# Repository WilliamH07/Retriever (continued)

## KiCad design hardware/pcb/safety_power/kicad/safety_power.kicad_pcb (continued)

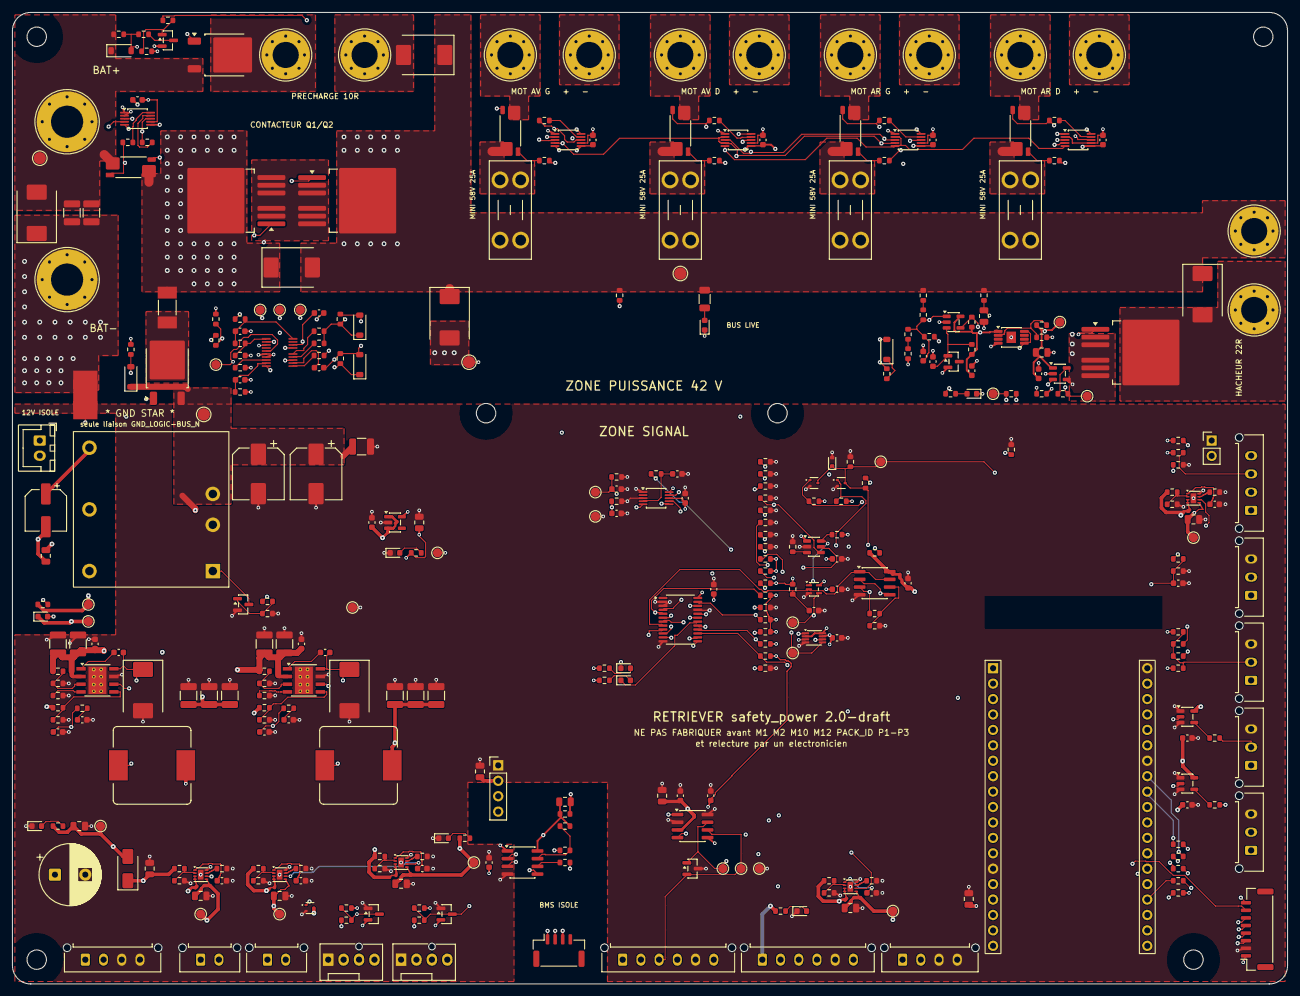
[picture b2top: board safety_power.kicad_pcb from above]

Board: 4 copper layers, 210.0 x 160.0 mm, 350 parts (0 on the bottom side), 190 nets.

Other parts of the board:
H1, H2, H3, H4, H5, H6: M3; MountingHole_3.2mm_M3

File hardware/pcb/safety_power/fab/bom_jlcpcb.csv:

Comment,Designator,Footprint,LCSC Part #
2.2µF 100V,"C1,C2,C51,CB121,CB122,CB51,CB52",C_1210_3225Metric,C153036
10µF 25V,"C10,C171,C181,C191,C201,C211,C52,C54,C57,C60,C78,C98",C_0805_2012Metric,C15850
100nF,"C11,C13,C40,C41,C42,C43,C62,C63,C64,C65,C67,C69,C71,C72,C73,C74,C75,C76,C79,C8,CB124,CB54",C_0603_1608Metric,C14663
1nF,"C12,C68",C_0603_1608Metric,C1588
1µF 25V,"C14,C53,C66,C7",C_0603_1608Metric,C5673
10nF,"C170,C180,C190,C200,C210,C70",C_0603_1608Metric,C57112
100nF 100V,"C4,CB123,CB53",C_0603_1608Metric,C88219
6.8nF,C5,C_0603_1608Metric,C1631
47µF 100V,"C50,C55",CP_Elec_8x10,C48935391
100µF 25V,C56,CP_Elec_6.3x7.7,C2836443
4.7µF 25V,"C61,C77",C_0805_2012Metric,C1779
1µF 100V,C9,C_0805_2012Metric,C385977
2200µF 10V,C99,CP_Radial_D10.0mm_P5.00mm,C49256788
15nF,CB125,C_0603_1608Metric,C107076
82pF C0G,"CB126,CB56",C_0603_1608Metric,C107056
22µF 25V,"CB127,CB128,CB129",C_1210_3225Metric,C52306
8.2nF,CB55,C_0603_1608Metric,C1322360
47µF 10V,"CB57,CB58,CB59",C_1210_3225Metric,C84494
SMCJ48CA,"D1,D2",D_SMC,C151287
KT-0603R,"D10,D11,D22",LED_0603_1608Metric,C2286
BZT52C12,"D12,D6",D_SOD-123,C43491
Everlight 19-217/GHC,"D13,D14,D15,D16,D17,D21",LED_0603_1608Metric,C72043
SS34,D18,D_SMA,C8678
NUP2105L,D19,SOT-23,C14486
ESD5Z3.3,D20,D_SOD-523,C397781
BAT54S,"D23,D24",SOT-23,C19726
B5819W,D26,D_SOD-123,C8598
SS510C,"D3,D7,D8",D_SMC,C19229
BZT52C15,"D4,D5",D_SOD-123,C173427
LM4040A25,D9,SOT-23,C9421
B560C,"DB12,DB5",D_SMC,C85100
5A 125V slo,F5,Fuse_Littelfuse-NANO2-451_453,C66503
Molex 43650-0415,"J11,J8,J9",Molex_Micro-Fit_3.0_43650-0415_1x04_P3.00mm_Vertical,C293547
Molex 43650-0315,"J14,J19,J20,J21",Molex_Micro-Fit_3.0_43650-0315_1x03_P3.00mm_Vertical,C293546
Molex 43650-0615,"J15,J16",Molex_Micro-Fit_3.0_43650-0615_1x06_P3.00mm_Vertical,C505231
IMU_BNO085,J17,JST_GH_SM08B-GHS-TB_1x08-1MP_P1.25mm_Horizontal,C265111
Molex 47053-1000,"J18A,J18B",FanPinHeader_1x04_P2.54mm_Vertical,C240840
BMS_UART (iso),J2,JST_GH_SM04B-GHS-TB_1x04-1MP_P1.25mm_Horizontal,C189895
Molex 43650-0215,"J22,J23",Molex_Micro-Fit_3.0_43650-0215_1x02_P3.00mm_Vertical,C293740
PWR_12V_COMPUTE,J7,JST_XH_B2B-XH-A_1x02_P2.50mm_Vertical,C265283
RADIO E-STOP,JP1,PinHeader_1x02_P2.54mm_Vertical,C492401
33µH,LB12,L_TaiTech_TMPC1265_13.5x12.5mm,C2847586
15µH,LB5,L_TaiTech_TMPC1265_13.5x12.5mm,C189912
URB4812YMD-30WR3,PS1,Mornsun_URB_YMD-30WR3_1x1in,C22458769
B0503S-1WR3,PS2,PinHeader_1x04_P2.54mm_Vertical,C5369462
IPB017N10N5LF,"Q1,Q2,Q5",TO-263-7_TabPin4_NoPin4,C3289286
DMG1012T,"Q10,Q8,Q9",SOT-523,C20512
SUD50P10-43L,"Q3,Q6",TO-252-2,C41408040
MMBT5551,"Q4,Q7",SOT-23,C2145
10Ω,"R1,R13,R14,R19,R29,R40,R41,R44,R45,R48,R49,R52,R53,R6",R_0603_1608Metric,C22859
100k,"R10,R100,R11,R110,R119,R120,R121,R122,R123,R124,R125,R126,R127,R132,R142,R18,R30,R31,R5,R62,R66,R80,R9,R90",R_0603_1608Metric,C25803
47k,"R101,R111,R81,R91",R_0603_1608Metric,C25819
4.42k,"R102,R112",R_0603_1608Metric,C23043
150k,"R12,R60",R_0603_1608Metric,C22807
10k,"R128,R129,R130,R131,R135,R136,R138,R140,R141,R145,R146,R147,R15,R153,R154,R165,R171,R173,R175,R21,R22,R28,R65,R71",R_0603_1608Metric,C25804
2.2k,"R133,R134,R92",R_0603_1608Metric,C4190
1k,"R137,R139,R143,R152,R155,R156,R63,R64,R85",R_0603_1608Metric,C21190
5.23k,R144,R_0603_1608Metric,C23068
20k,R148,R_0603_1608Metric,C4184
57.6k,R149,R_0603_1608Metric,C23082
18.7k,R150,R_0603_1608Metric,C22893
24.3k,R151,R_0603_1608Metric,C23348
0R,R158,R_0603_1608Metric,C21189
22k,R16,R_0603_1608Metric,C31850
33Ω,"R161,R162,R163,R164",R_0603_1608Metric,C23140
470Ω,"R166,R167",R_0603_1608Metric,C23179
330Ω,"R168,R34",R_0603_1608Metric,C23138
100Ω,"R169,R170",R_0603_1608Metric,C22775
4.7k,"R17,R172,R174,R33,R67,R75",R_0603_1608Metric,C23162
1M,R2,R_0603_1608Metric,C22935
93.1k,R20,R_0603_1608Metric,C228101
49.9k,"R23,R24",R_0603_1608Metric,C23184
6.04k,R25,R_0603_1608Metric,C25977
221Ω,R26,R_0603_1608Metric,C23342
1.69M,R27,R_0603_1608Metric,C247054
51k,R3,R_0603_1608Metric,C23196
33k,R32,R_0603_1608Metric,C4216
40.2k,R4,R_0603_1608Metric,C12447
22k,R61,R_1206_3216Metric,C114942
150Ω,"R7,R8",R_0603_1608Metric,C22808
124k,R70,R_0603_1608Metric,C22788
1.05k,R72,R_0603_1608Metric,C858882
1.4k,R82,R_0603_1608Metric,C25957
1.18M,"RB121,RB51",R_0603_1608Metric,C4072929
59k,"RB122,RB52",R_0603_1608Metric,C23085
243k,"RB123,RB53",R_0603_1608Metric,C23351
143k,RB124,R_0603_1608Metric,C304703
10.2k,"RB125,RB55",R_0603_1608Metric,C22772
10.5k,RB126,R_0603_1608Metric,C22855
53.6k,RB54,R_0603_1608Metric,C23074
10.7k,RB56,R_0603_1608Metric,C22857
1mΩ WSK2512,RS1,R_Shunt_Vishay_WSK2512_6332Metric_T1.19mm,C4248455
2mΩ WSK2512,"RS2,RS3,RS4,RS5",R_Shunt_Vishay_WSK2512_6332Metric_T1.19mm,C3997408
TPS48100QDGXRQ1,U1,TI_DGX0019A_VSSOP-19,C43131316
TPS259573,U10,Texas_DSG0008A_WSON-8-1EP_2x2mm_P0.5mm_EP0.9x1.6mm,C2653844
TPS259531,"U11,U12,U13,U14",Texas_DSG0008A_WSON-8-1EP_2x2mm_P0.5mm_EP0.9x1.6mm,C2155674
TCAN1042HVDRQ1,U16,SOIC-8_3.9x4.9mm_P1.27mm,C485807
TPL5010,U17,SOT-23-6,C473912
74LVC1G08,U18,SOT-353_SC-70-5,C12512
SN74LVC1G74,U19,VSSOP-8_2.3x2mm_P0.5mm,C70285
INA228,"U2,U6,U7,U8,U9",TSSOP-10_3x3mm_P0.5mm,C2887910
LM2903,U20,SOIC-8_3.9x4.9mm_P1.27mm,C7549
ADS1115,U21,TSSOP-10_3x3mm_P0.5mm,C37593
TCA9555,U22,TSSOP-24_4.4x7.8mm_P0.65mm,C465732
74AHCT1G125,"U23,U24",SOT-23-5,C7484
ADuM1201,U25,SOIC-8_3.9x4.9mm_P1.27mm,C9669
AP2112K-3.3,U26,SOT-23-5,C51118
TPS7A4001,U3,HVSSOP-8-1EP_3x3mm_P0.65mm_EP1.57x1.89mm,C5144143
TLV1701,U4,SOT-23-5,C130035
UCC27517,U5,SOT-23-5,C99395
TPS54360BDDAR,"UB12,UB5",TI_SO-PowerPAD-8_ThermalVias,C524806

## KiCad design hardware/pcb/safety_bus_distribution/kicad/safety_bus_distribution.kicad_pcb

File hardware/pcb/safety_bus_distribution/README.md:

# Safety bus distribution board

> **v2.0 is designed** — schematic and layout generated, ERC and DRC clean,
> not yet fabricated. Every choice and its reason: [`decisions.md`](decisions.md)
> (French). Brief: [`cahier-des-charges.md`](cahier-des-charges.md).

| | |
|---|---|
| Size | 110 × 72 mm, 2 layers, 4 × M3 |
| Parts | 122 placed by the assembler, 9 Micro-Fit connectors through-hole |
| Per branch | eFuse `TPS259531` (≈0.95 A), ground PPTC 1.1 A / 48 V, CAN choke `ACT45B`, `NUP2105L` |
| Sources | [`kicad/`](kicad/) — KiCad 10 project, **generated** by [`scripts/build.py`](scripts/build.py) |
| Fabrication | [`fab/`](fab/) — Gerber zip, JLCPCB BOM and placement, schematic PDF, renders |

Rebuild everything: `./build.sh` then `./fab.sh` (needs the toolchain in
[`../outils.md`](../outils.md)). Do not edit the KiCad files by hand: change
`scripts/build.py` and rebuild, or the next build overwrites the change.

Carries the CAN bus and the `/SAFE` line to every node, and feeds each of them
5 V through its own protection. One trunk in, eight branches out.

**It has no microcontroller, and that is the point.** A board that sits on the
safety path and can crash, hang, or need reflashing is a liability. Everything
here is passive or analogue. There is nothing to debug at three in the morning.

It replaces the board previously called `can_distribution`. The rename is not
cosmetic: the `/SAFE` line runs to exactly the same four nodes as the CAN bus,
over exactly the same route. Pulling two looms side by side would have been
absurd.

## Why this board is built first

It is the only one of the three that no measurement blocks. `motor_interface`
waits on the Hall signal levels, `safety_power` waits on the BMS cut-off
threshold and the pack identity. This one waits on nothing.

Building it first puts three ESP32s on a working CAN bus on the bench within a
week, which is where the firmware, the frame protocol and `protocol.yaml` get
written — while the power measurements happen in parallel. That is the correct
use of the critical path.

## The trunk

Six conductors, one connector type, everywhere on the robot.

| Pin | Net | Wire |
|---|---|---|
| 1 | `5V_LOGIC` | orange |
| 2 | `CANH` | green |
| 3 | `CANL` | brown |
| 4 | `/SAFE` | violet |
| 5 | `GND_LOGIC` | black, white tracer |
| 6 | `SHIELD` | — |

Molex Micro-Fit 3.0, 6 circuits, 600 V, positive latch, 5.5 A per circuit at
20 AWG. Every node gets **two in parallel** so the bus passes through it without
a stub.

Violet is reserved for `/SAFE` itself. The e-stop loops and the brake command use
violet with a tracer — close enough to read as "safety" at a glance, distinct
enough that you cannot splice one into the other.

## Topology, stated plainly

A board with eight connectors *is* a star, and ISO 11898-2 asks for a line with
two terminations and short drops. At 500 kbit/s the bit time is 2 µs and a 30 cm
stub costs about 3 ns round trip, so a star works comfortably. That is not the
problem.

The problem is that if nobody writes it down, somebody eventually adds a three
metre drop. So the rule is on the silkscreen: **`STUB MAX 30 cm`**.

```
   Daisy chain — the normal case      Star — bench and fault-finding
   ┌───┐  ┌───┐  ┌───┐                     ┌──── trunk ────┐
   │IN │──│OUT│  │IN │── …                 │  │  │  │  │  │
   └───┘  └───┘  └───┘                    n1 n2 n3 n4 n5 n6
   120 Ω at the two physical ends      120 Ω on two branches only
```

## Termination you can verify

Split termination, always: 2 × 60 Ω with `CSPLIT` from the midpoint to ground.
It costs one capacitor and it cuts common-mode emission sharply. On a robot
where the CAN pair runs past four BLDC choppers, that is not a refinement.

Selectable by jumper at two positions, each with its own blue LED, so a glance
tells you how many are active.

And the acceptance test is printed on the board, because a termination jumper is
the classic thing nobody can account for six months later:

> **Bus unpowered, measure between `TP_CANH` and `TP_CANL`:**
> **60 Ω → correct.** 120 Ω → only one termination. 40 Ω → three.

Five seconds, no instrument beyond a multimeter.

## Per branch, and why each part is there

| Part | Against |
|---|---|
| `TCAN1042HVDR` at each node — not on this board | A power line touching `CANH`. See below |
| `NUP2105L` across CANH/CANL | ESD and **transients only** — see the caveat below. Clamps to 40 V at 5 A, where a `PESD1CAN` needs 70 V at 3 A |
| `ACT45B-510-2P-TL003` common mode choke | The 16–20 kHz chopping coupled from the phase wires. 200 mA rated, 1 Ω DCR |
| `1812L050/30` PPTC on the 5 V feed | One node shorting must not take down the other seven |
| **PPTC 500 mA in series with the branch ground** | The failure nobody plans for — see below |
| One green LED per branch | Knowing at a glance which node is actually powered |

### The transceiver choice belongs here even though the part sits elsewhere

The `SN65HVD230` in the original architecture is rated **−4 V to +16 V** on its
bus pins. This robot runs a 42 V rail in the same loom. A single contact between
a power conductor and `CANH` destroys **every transceiver on the bus at once** —
all four nodes, simultaneously.

The `TCAN1042HV` is rated **±70 V**. The same fault becomes survivable. It costs
a 5 V rail on each node instead of running natively at 3.3 V, and the `VIO` pin
handles the logic side. That is a good trade.

⚠️ **But do not oversell it.** The `NUP2105L` on every branch has a 24 V standoff
and breaks down between 26 and 32 V. A **sustained** 42 V contact makes it
conduct continuously and destroys it — on all eight branches — whatever the
transceiver is rated for. The TVS survives transients, not a permanent fault; it
fails short, which at least pulls the bus down visibly rather than letting the
fault propagate. The transceiver's ±70 V rating is what saves the *nodes*, and
the branch ground PPTC is what stops the fault current. Replacing eight TVS
diodes after a wiring mistake is the acceptable outcome here — not the same as
"nothing breaks".

Two things that will cost you an afternoon if you miss them: `STB` has an
internal pull-up, so **a floating `STB` pin silently puts the transceiver in
standby** — tie it to ground. And it is the `V` suffix, not the `H`, that brings
the `VIO` pin.

### The ground fuse

If a node's ground comes loose on the power side while the CAN cable stays
plugged in, that node's entire return current goes through a 0.5 mm² conductor
sized for a few tens of milliamps. It melts, or it heats and drags every ground
reference on the robot with it.

A 500 mA PPTC in series with each branch ground costs twenty cents and turns
that into a node that simply stops talking.

## `/SAFE`

Active low, open drain, wired-OR, referenced to **3.3 V** — not 5 V, so it lands
directly on an ESP32 pin with no level shifting.

**One** pull-up in the whole system: 1 kΩ to `3V3_HOTEL` on `safety_power`, **in
series with the mushroom's NC contact**. **One** pull-down, also on
`safety_power`: 10 kΩ. Every other board carries a 1 MΩ pull-down only, to define
its own state when it is unplugged from the trunk.

> A first draft of this board put a 10 kΩ pull-down on *every* board. With three
> boards that is 3.33 kΩ against a 4.7 kΩ pull-up: the high level lands at
> **2.07 V**, below the ESP32's 2.48 V VIH. The line would have read low
> permanently and the robot would never have released its brakes. One pull-up,
> one pull-down, and a level calculation written down — 3.3 × 10/(1+10) =
> **3.00 V**, 0.52 V of margin.

The mushroom's contact is **normally closed and in series with the pull-up**, not
across the line to ground. Released, the contact is closed, the pull-up is
connected, the line is high, the robot is permitted to run. Pressed — or the wire
cut, or the connector unplugged — the pull-up is disconnected and the pull-down
takes the line to ground. That is the only arrangement worth having, and it is
the opposite of what "NC contact pulls the line low" would suggest.

> ⚠️ **Read this before wiring `/SAFE` to the motor controllers.** Pulling
> `/SAFE` low does **not** brake the motors. On the ZS-X11H, `STOP` is active
> low and puts the drive into **coast**, and `BRAKE` is active **high**, so a
> released line releases the brake. The two-stage e-stop described in the
> architecture dossier assumes the opposite. The fix lives on
> `motor_interface` — a pull-up to 5 V sitting **on the loom, at the controller
> end**, which an open-drain MOSFET contradicts only while a hardware AND gate
> sees both `/SAFE` high and a live MCU. Lose any of them and `BRAKE` goes high.
> Putting the pull-up on the loom rather than the board is what makes unplugging
> the board brake rather than coast. See that board's specification.

## Node allocation

| Branch | Node |
|---|---|
| 1 | ESP32-SAFETY, on `safety_power` |
| 2 | ESP32-MOTION front |
| 3 | ESP32-MOTION rear |
| 4 | USB-CAN adapter to the X1 — `candleLight`/`gs_usb` firmware, not `slcan` |
| 5–7 | free — arm, turret, smart sensor, fifth wheel |
| 8 | bench |

Four nodes today, eight positions. The architecture brief asked for growth
without rewiring; this is what that looks like in copper.

## Bus load, for reference

675 frames per second at roughly 110 bits each, on 500 kbit/s, is about **15 %**
occupancy. There is a great deal of room.

## Bring up

Never plug a new board into the robot.

1. **Continuity.** Trunk pin *n* to branch pin *n*, eight branches, six pins.
   Then confirm no continuity between neighbours. Forty-eight measurements plus
   the shorts check.
2. **Terminations off, ohmmeter across `TP_CANH`/`TP_CANL`.** Expect open.
   Fit one jumper: 120 Ω. Fit the second: **60 Ω.**
3. **5 V alone** on the trunk, nothing else connected. Eight green LEDs.
   Current draw of a few milliamps. Above 50 mA, stop and find the short.
4. **`/SAFE` idle.** With the trunk pull-up present, every branch reads high.
   Short `/SAFE` to ground at any branch: every branch reads low. That is the
   wired-OR working.
5. **Two nodes, loopback.** Two ESP32s, 500 kbit/s, one sending, one receiving.
   Then unplug one mid-traffic and watch the other go bus-off and recover with
   `restart-ms 100`.
6. **Ground fuse.** Deliberately draw 1 A through a branch ground. The PPTC
   should trip. Better to learn this on the bench than in the field.

## Status

Specified. Nothing blocks it — no measurement, no pending decision. It is the
board to draw first.

Connector-by-connector pinout in [`hardware/icd.yaml`](../../icd.yaml).
Component justifications, with datasheet URLs, in
[`09-validation-composants.md`](../../../docs/architecture/09-validation-composants.md).

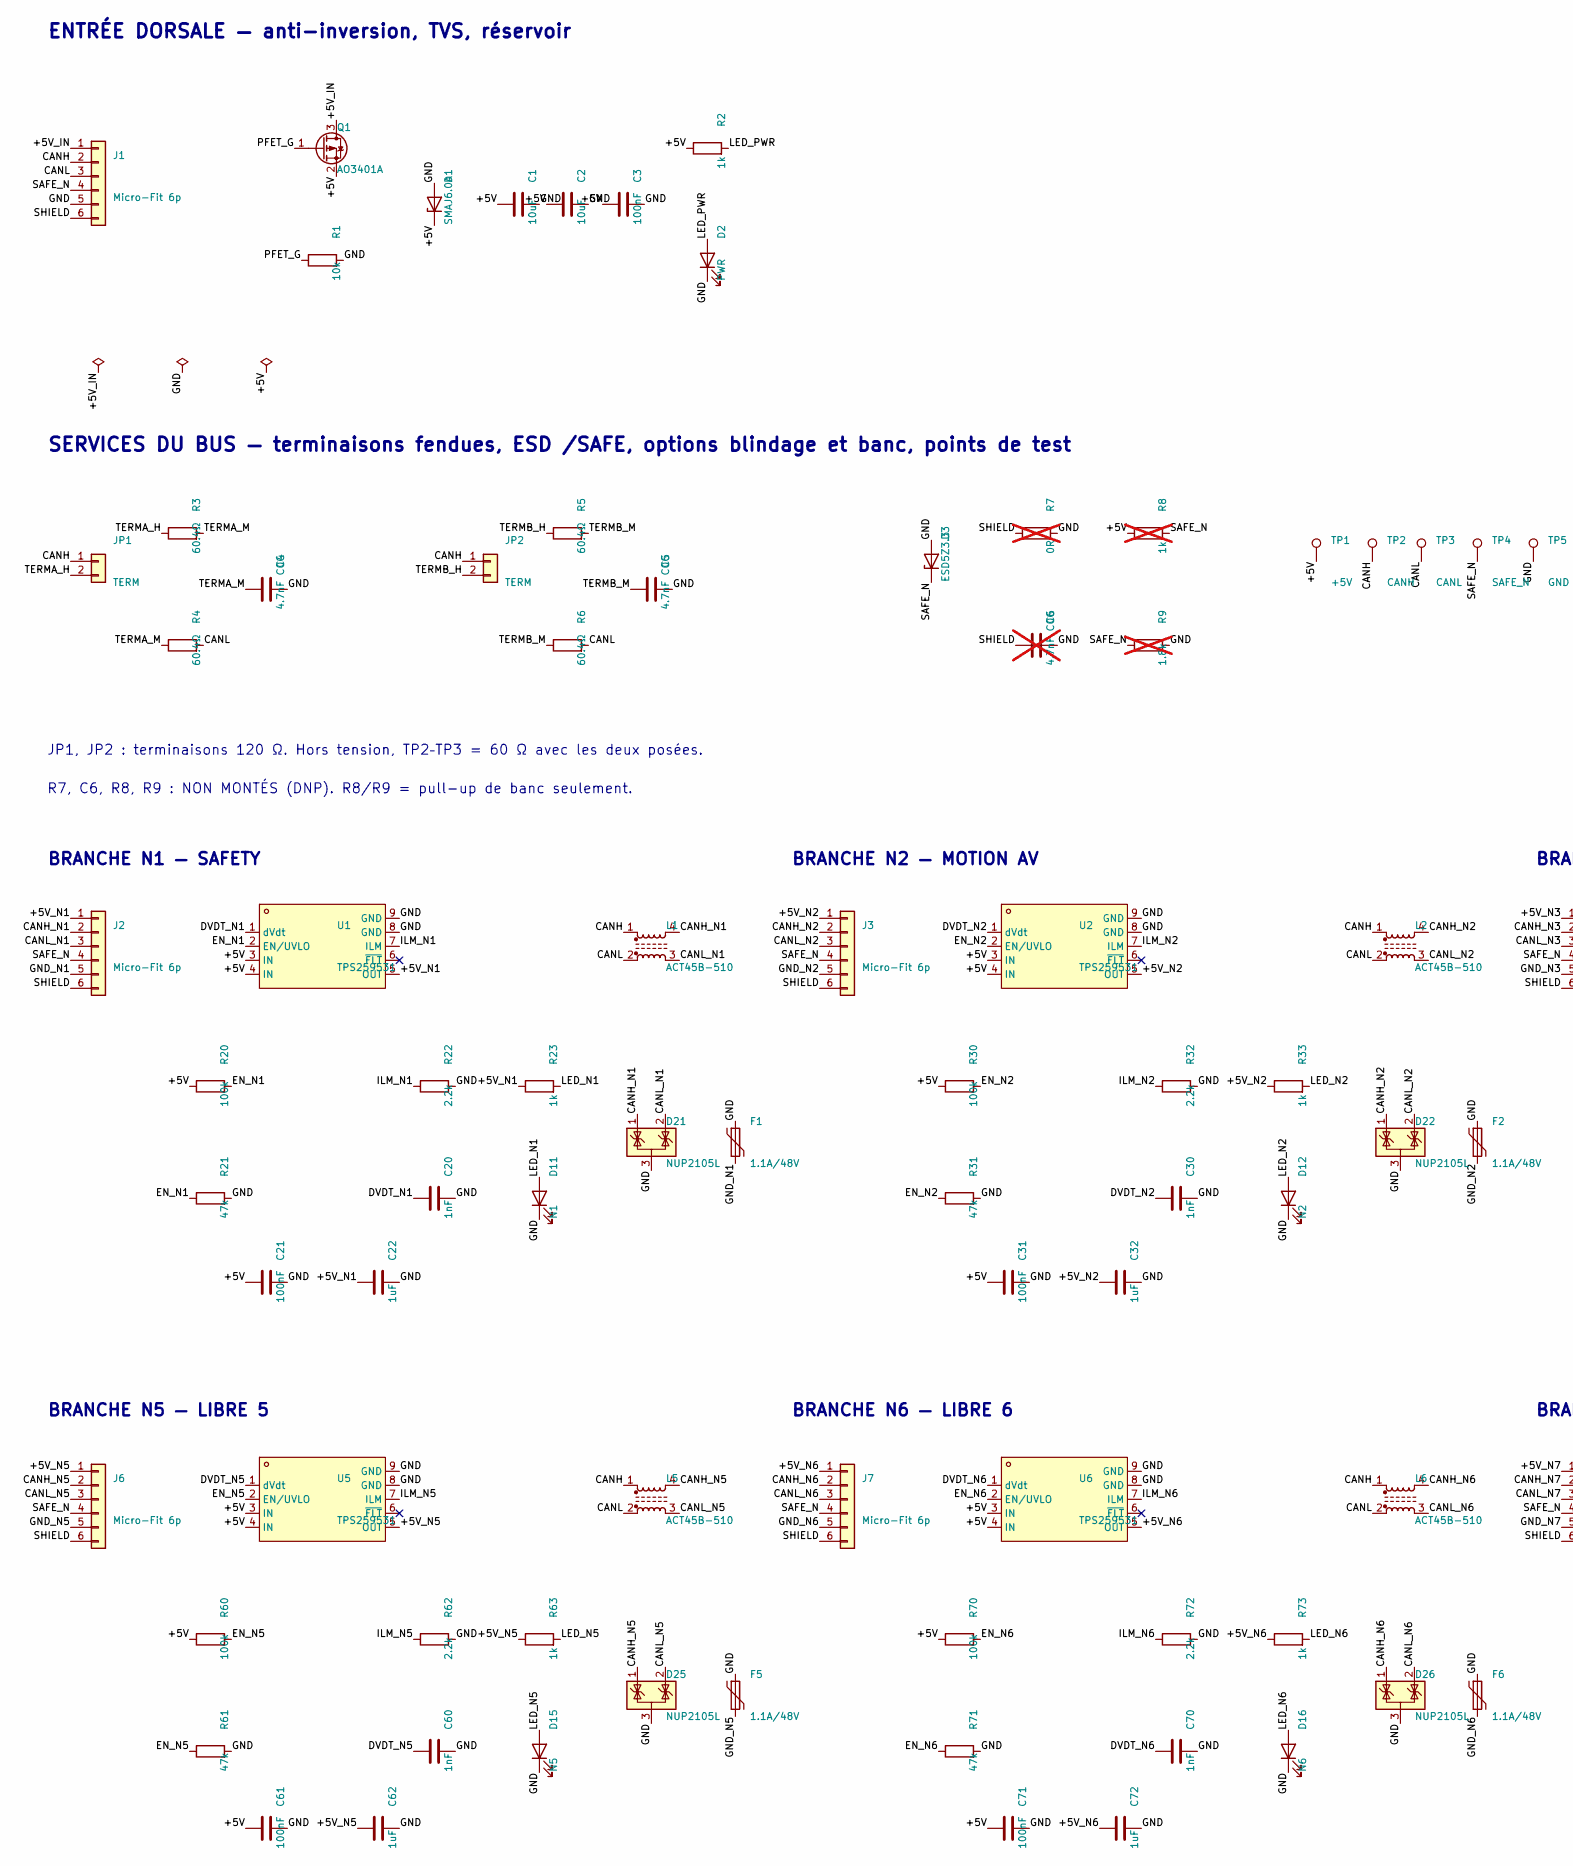
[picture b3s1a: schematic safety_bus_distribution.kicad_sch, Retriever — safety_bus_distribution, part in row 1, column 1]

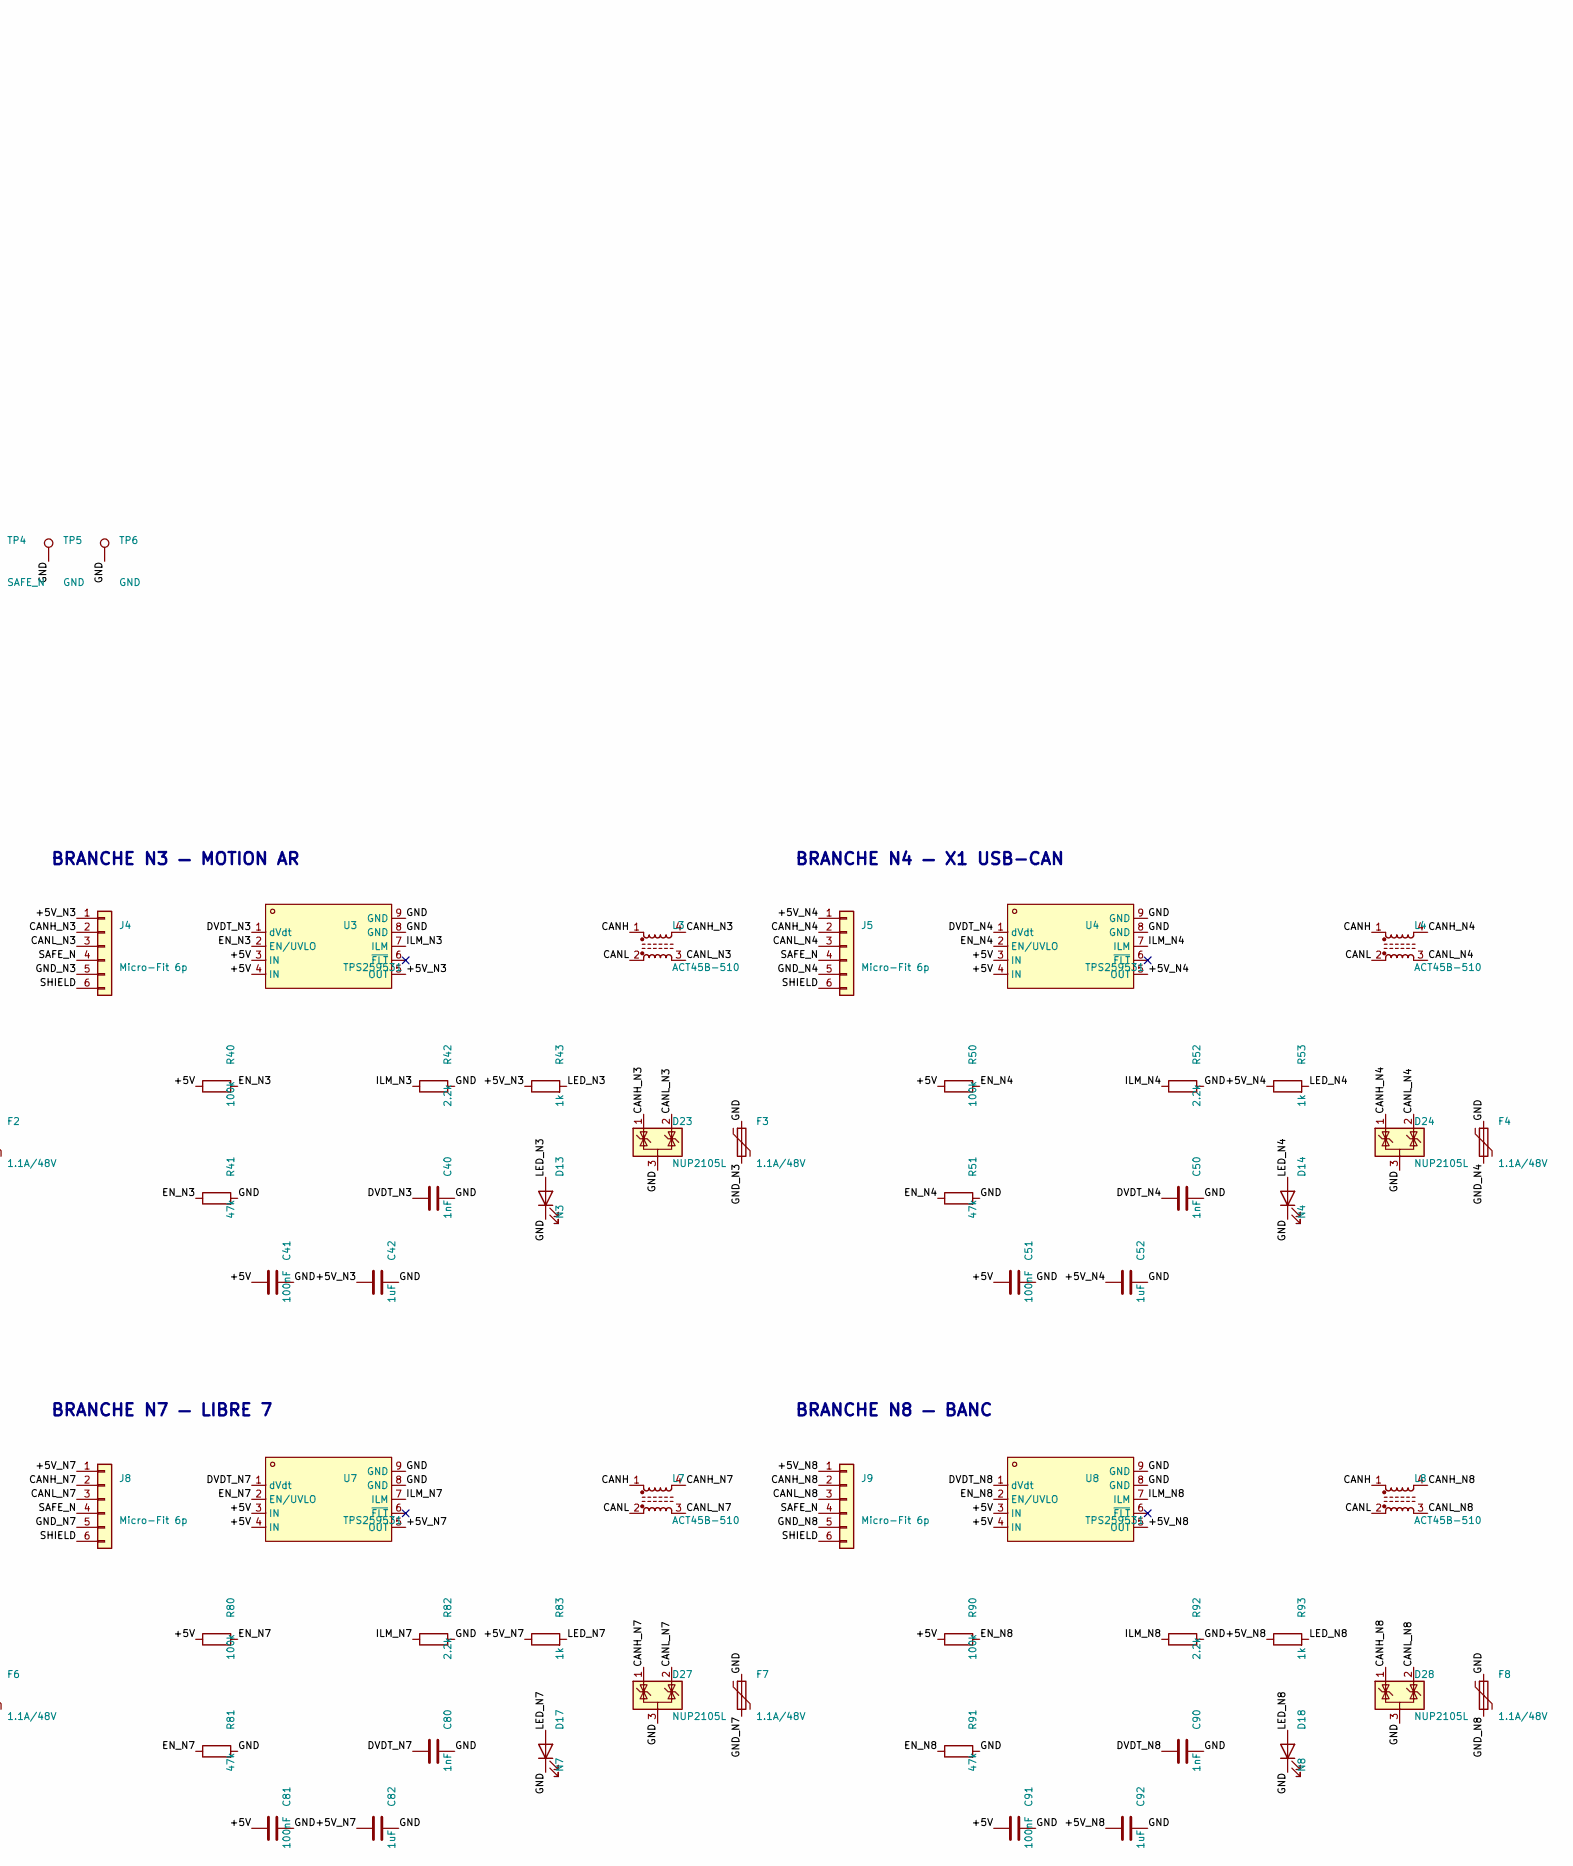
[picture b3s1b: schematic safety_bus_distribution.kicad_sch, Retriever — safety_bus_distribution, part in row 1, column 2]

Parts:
C1, C2: 10uF; C_0805_2012Metric; MPN CL21A106KAYNNNE; LCSC C15850
C3, C21, C31, C41, C51, C61, C71, C81, C91: 100nF; C_0603_1608Metric; MPN CC0603KRX7R9BB104; LCSC C14663
C4, C5: 4.7nF C0G; C_0603_1608Metric; MPN GRM1885C1H472JA01D; LCSC C85980
C6: 4.7nF C0G; C_0603_1608Metric; MPN GRM1885C1H472JA01D; LCSC C85980; not fitted
C20, C30, C40, C50, C60, C70, C80, C90: 1nF; C_0603_1608Metric; MPN 0603B102K500NT; LCSC C1588
C22, C32, C42, C52, C62, C72, C82, C92: 1uF; C_0603_1608Metric; MPN CL10A105KB8NNNC; LCSC C15849
D1: SMAJ6.0A; D_SMA; MPN Littelfuse SMAJ6.0A; LCSC C223993
D2: PWR; LED_0603_1608Metric; MPN Everlight 19-217/GHC; LCSC C72043
D3: ESD5Z3.3; D_SOD-523; MPN ESD5Z3.3T1G; LCSC C5252448
D11: N1; LED_0603_1608Metric; MPN Everlight 19-217/GHC; LCSC C72043
D12: N2; LED_0603_1608Metric; MPN Everlight 19-217/GHC; LCSC C72043
D13: N3; LED_0603_1608Metric; MPN Everlight 19-217/GHC; LCSC C72043
D14: N4; LED_0603_1608Metric; MPN Everlight 19-217/GHC; LCSC C72043
D15: N5; LED_0603_1608Metric; MPN Everlight 19-217/GHC; LCSC C72043
D16: N6; LED_0603_1608Metric; MPN Everlight 19-217/GHC; LCSC C72043
D17: N7; LED_0603_1608Metric; MPN Everlight 19-217/GHC; LCSC C72043
D18: N8; LED_0603_1608Metric; MPN Everlight 19-217/GHC; LCSC C72043
D21, D22, D23, D24, D25, D26, D27, D28: NUP2105L; SOT-23; MPN onsemi NUP2105LT1G; LCSC C14486
F1, F2, F3, F4, F5, F6, F7, F8: 1.1A/48V; F1812; MPN LUTE 1812L110/48QR; LCSC C19723490
J1, J2, J3, J4, J5, J6, J7, J8, J9: Micro-Fit 6p; Molex_Micro-Fit_3.0_43650-0615_1x06_P3.00mm_Vertical; MPN Molex 43650-0615; LCSC C505231
JP1, JP2: TERM; PinHeader_1x02_P2.54mm_Vertical; MPN 2.54 mm 1x2 header; LCSC C492401
L1, L2, L3, L4, L5, L6, L7, L8: ACT45B-510; IND-SMD_4P-L4.5-W3.2-TL; MPN TDK ACT45B-510-2P-TL003; LCSC C76584
Q1: AO3401A; SOT-23; MPN AOS AO3401A; LCSC C15127
R1: 10k; R_0603_1608Metric; MPN 0603WAF1002T5E; LCSC C25804
R2, R23, R33, R43, R53, R63, R73, R83, R93: 1k; R_0603_1608Metric; MPN 0603WAF1001T5E; LCSC C21190
R3, R4, R5, R6: 60.4Ω; R_0603_1608Metric; MPN RM06F60R4CT; LCSC C4099359
R7: 0R; R_0603_1608Metric; MPN 0603WAF0000T5E; LCSC C21189; not fitted
R8: 1k; R_0603_1608Metric; MPN 0603WAF1001T5E; LCSC C21190; not fitted
R9: 1.8k; R_0603_1608Metric; MPN 0603WAF1801T5E; LCSC C4177; not fitted
R20, R30, R40, R50, R60, R70, R80, R90: 100k; R_0603_1608Metric; MPN 0603WAF1003T5E; LCSC C25803
R21, R31, R41, R51, R61, R71, R81, R91: 47k; R_0603_1608Metric; MPN 0603WAF4702T5E; LCSC C25819
R22, R32, R42, R52, R62, R72, R82, R92: 2.2k; R_0603_1608Metric; MPN 0603WAF2201T5E; LCSC C4190
TP1: +5V; TestPoint_Pad_D1.5mm
TP2: CANH; TestPoint_Pad_D1.5mm
TP3: CANL; TestPoint_Pad_D1.5mm
TP4: SAFE_N; TestPoint_Pad_D1.5mm
TP5, TP6: GND; TestPoint_Pad_D1.5mm
U1, U2, U3, U4, U5, U6, U7, U8: TPS259531; Texas_DSG0008A_WSON-8-1EP_2x2mm_P0.5mm_EP0.9x1.6mm; MPN TI TPS259531DSGR; LCSC C2155674

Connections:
/+5V: C1.1, C2.1, C3.1, C21.1, C31.1, C41.1, C51.1, C61.1, C71.1, C81.1, C91.1, D1.1 (K), Q1.2 (S), R2.1, R8.1, R20.1, R30.1, R40.1, R50.1, R60.1, R70.1, R80.1, R90.1, TP1.1, U1.3 (IN), U1.4 (IN), U2.3 (IN), U2.4 (IN), U3.3 (IN), U3.4 (IN), U4.3 (IN), U4.4 (IN), U5.3 (IN), U5.4 (IN), U6.3 (IN), U6.4 (IN), U7.3 (IN), U7.4 (IN), U8.3 (IN), U8.4 (IN)
/+5V_IN: J1.1, Q1.3 (D)
/+5V_N1: C22.1, J2.1, R23.1, U1.5 (OUT)
/+5V_N2: C32.1, J3.1, R33.1, U2.5 (OUT)
/+5V_N3: C42.1, J4.1, R43.1, U3.5 (OUT)
/+5V_N4: C52.1, J5.1, R53.1, U4.5 (OUT)
/+5V_N5: C62.1, J6.1, R63.1, U5.5 (OUT)
/+5V_N6: C72.1, J7.1, R73.1, U6.5 (OUT)
/+5V_N7: C82.1, J8.1, R83.1, U7.5 (OUT)
/+5V_N8: C92.1, J9.1, R93.1, U8.5 (OUT)
/CANH: J1.2, JP1.1, JP2.1, L1.1, L2.1, L3.1, L4.1, L5.1, L6.1, L7.1, L8.1, TP2.1
/CANH_N1: D21.1 (K), J2.2, L1.4
/CANH_N2: D22.1 (K), J3.2, L2.4
/CANH_N3: D23.1 (K), J4.2, L3.4
/CANH_N4: D24.1 (K), J5.2, L4.4
/CANH_N5: D25.1 (K), J6.2, L5.4
/CANH_N6: D26.1 (K), J7.2, L6.4
/CANH_N7: D27.1 (K), J8.2, L7.4
/CANH_N8: D28.1 (K), J9.2, L8.4
/CANL: J1.3, L1.2, L2.2, L3.2, L4.2, L5.2, L6.2, L7.2, L8.2, R4.2, R6.2, TP3.1
/CANL_N1: D21.2 (K), J2.3, L1.3
/CANL_N2: D22.2 (K), J3.3, L2.3
/CANL_N3: D23.2 (K), J4.3, L3.3
/CANL_N4: D24.2 (K), J5.3, L4.3
/CANL_N5: D25.2 (K), J6.3, L5.3
/CANL_N6: D26.2 (K), J7.3, L6.3
/CANL_N7: D27.2 (K), J8.3, L7.3
/CANL_N8: D28.2 (K), J9.3, L8.3
/DVDT_N1: C20.1, U1.1 (dVdt)
/DVDT_N2: C30.1, U2.1 (dVdt)
/DVDT_N3: C40.1, U3.1 (dVdt)
/DVDT_N4: C50.1, U4.1 (dVdt)
/DVDT_N5: C60.1, U5.1 (dVdt)
/DVDT_N6: C70.1, U6.1 (dVdt)
/DVDT_N7: C80.1, U7.1 (dVdt)
/DVDT_N8: C90.1, U8.1 (dVdt)
/EN_N1: R20.2, R21.1, U1.2 (EN/UVLO)
/EN_N2: R30.2, R31.1, U2.2 (EN/UVLO)
/EN_N3: R40.2, R41.1, U3.2 (EN/UVLO)
/EN_N4: R50.2, R51.1, U4.2 (EN/UVLO)
/EN_N5: R60.2, R61.1, U5.2 (EN/UVLO)
/EN_N6: R70.2, R71.1, U6.2 (EN/UVLO)
/EN_N7: R80.2, R81.1, U7.2 (EN/UVLO)
/EN_N8: R90.2, R91.1, U8.2 (EN/UVLO)
/GND: C1.2, C2.2, C3.2, C4.2, C5.2, C6.2, C20.2, C21.2, C22.2, C30.2, C31.2, C32.2, C40.2, C41.2, C42.2, C50.2, C51.2, C52.2, C60.2, C61.2, C62.2, C70.2, C71.2, C72.2, C80.2, C81.2, C82.2, C90.2, C91.2, C92.2, D1.2 (A), D2.1 (K), D3.2 (A), D11.1 (K), D12.1 (K), D13.1 (K), D14.1 (K), D15.1 (K), D16.1 (K), D17.1 (K), D18.1 (K), D21.3 (A), D22.3 (A), D23.3 (A), D24.3 (A), D25.3 (A), D26.3 (A), D27.3 (A), D28.3 (A), F1.1, F2.1, F3.1, F4.1, F5.1, F6.1, F7.1, F8.1, J1.5, R1.2, R7.2, R9.2, R21.2, R22.2, R31.2, R32.2, R41.2, R42.2, R51.2, R52.2, R61.2, R62.2, R71.2, R72.2, R81.2, R82.2, R91.2, R92.2, TP5.1, TP6.1, U1.8 (GND), U1.9 (GND), U2.8 (GND), U2.9 (GND), U3.8 (GND), U3.9 (GND), U4.8 (GND), U4.9 (GND), U5.8 (GND), U5.9 (GND), U6.8 (GND), U6.9 (GND), U7.8 (GND), U7.9 (GND), U8.8 (GND), U8.9 (GND)
/GND_N1: F1.2, J2.5
/GND_N2: F2.2, J3.5
/GND_N3: F3.2, J4.5
/GND_N4: F4.2, J5.5
/GND_N5: F5.2, J6.5
/GND_N6: F6.2, J7.5
/GND_N7: F7.2, J8.5
/GND_N8: F8.2, J9.5
/ILM_N1: R22.1, U1.7 (ILM)
/ILM_N2: R32.1, U2.7 (ILM)
/ILM_N3: R42.1, U3.7 (ILM)
/ILM_N4: R52.1, U4.7 (ILM)
/ILM_N5: R62.1, U5.7 (ILM)
/ILM_N6: R72.1, U6.7 (ILM)
/ILM_N7: R82.1, U7.7 (ILM)
/ILM_N8: R92.1, U8.7 (ILM)
/LED_N1: D11.2 (A), R23.2
/LED_N2: D12.2 (A), R33.2
/LED_N3: D13.2 (A), R43.2
/LED_N4: D14.2 (A), R53.2
/LED_N5: D15.2 (A), R63.2
/LED_N6: D16.2 (A), R73.2
/LED_N7: D17.2 (A), R83.2
/LED_N8: D18.2 (A), R93.2
/LED_PWR: D2.2 (A), R2.2
/PFET_G: Q1.1 (G), R1.1
/SAFE_N: D3.1 (K), J1.4, J2.4, J3.4, J4.4, J5.4, J6.4, J7.4, J8.4, J9.4, R8.2, R9.1, TP4.1
/SHIELD: C6.1, J1.6, J2.6, J3.6, J4.6, J5.6, J6.6, J7.6, J8.6, J9.6, R7.1
/TERMA_H: JP1.2, R3.1
/TERMA_M: C4.1, R3.2, R4.1
/TERMB_H: JP2.2, R5.1
/TERMB_M: C5.1, R5.2, R6.1

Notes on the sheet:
ENTRÉE DORSALE — anti-inversion, TVS, réservoir
SERVICES DU BUS — terminaisons fendues, ESD /SAFE, options blindage et banc, points de test
JP1, JP2 : terminaisons 120 Ω. Hors tension, TP2–TP3 = 60 Ω avec les deux posées.
R7, C6, R8, R9 : NON MONTÉS (DNP). R8/R9 = pull-up de banc seulement.
BRANCHE N1 — SAFETY
BRANCHE N2 — MOTION AV
BRANCHE N3 — MOTION AR
BRANCHE N4 — X1 USB-CAN
BRANCHE N5 — LIBRE 5
BRANCHE N6 — LIBRE 6
BRANCHE N7 — LIBRE 7
BRANCHE N8 — BANC

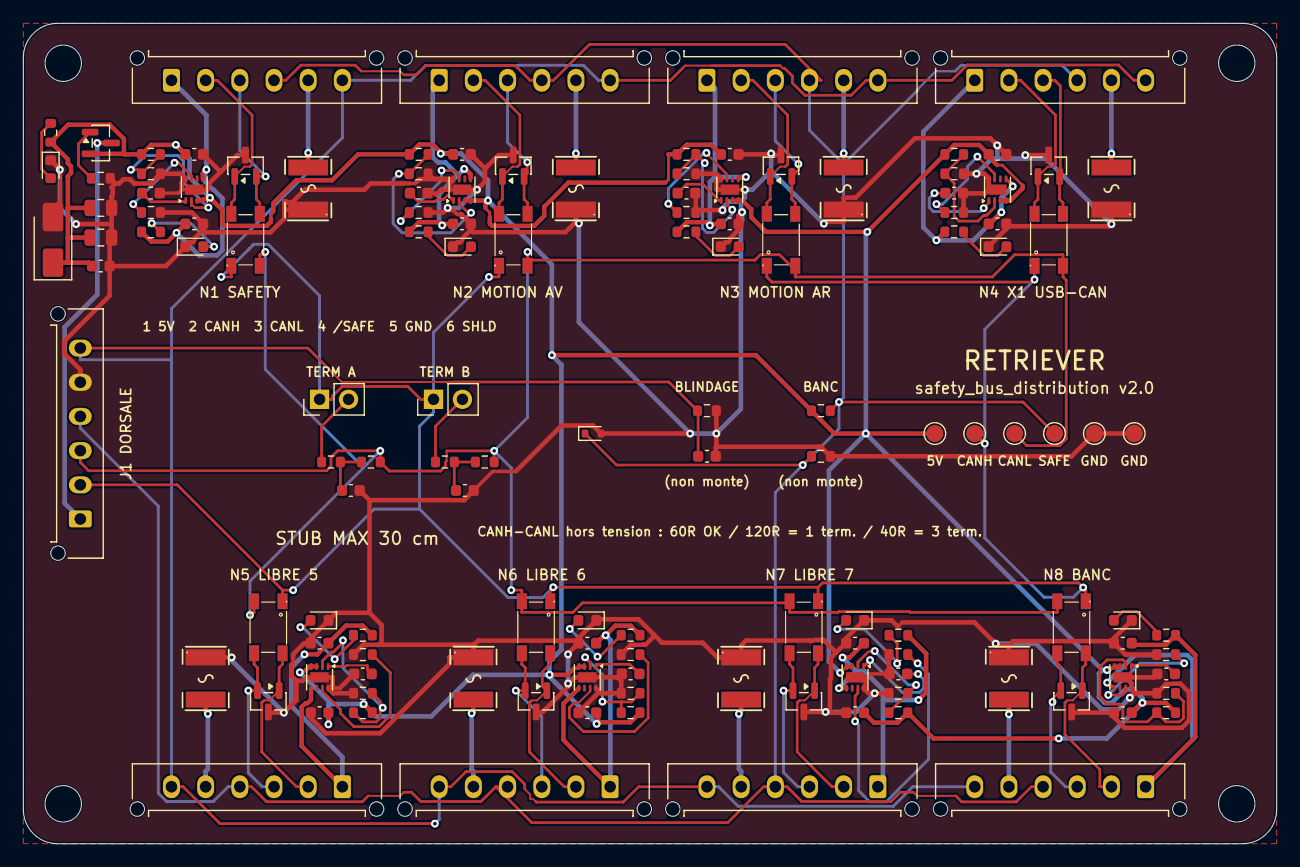
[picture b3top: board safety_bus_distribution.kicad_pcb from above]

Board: 2 copper layers, 110.0 x 72.0 mm, 136 parts (0 on the bottom side), 77 nets.

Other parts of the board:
H1, H2, H3, H4: M3; MountingHole_3.2mm_M3

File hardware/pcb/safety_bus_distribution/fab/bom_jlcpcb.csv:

Comment,Designator,Footprint,LCSC Part #
10uF,"C1,C2",C_0805_2012Metric,C15850
1nF,"C20,C30,C40,C50,C60,C70,C80,C90",C_0603_1608Metric,C1588
100nF,"C21,C3,C31,C41,C51,C61,C71,C81,C91",C_0603_1608Metric,C14663
1uF,"C22,C32,C42,C52,C62,C72,C82,C92",C_0603_1608Metric,C15849
4.7nF C0G,"C4,C5",C_0603_1608Metric,C85980
SMAJ6.0A,D1,D_SMA,C223993
Everlight 19-217/GHC,"D11,D12,D13,D14,D15,D16,D17,D18,D2",LED_0603_1608Metric,C72043
NUP2105L,"D21,D22,D23,D24,D25,D26,D27,D28",SOT-23,C14486
ESD5Z3.3,D3,D_SOD-523,C5252448
1.1A/48V,"F1,F2,F3,F4,F5,F6,F7,F8",F1812,C19723490
Micro-Fit 6p,"J1,J2,J3,J4,J5,J6,J7,J8,J9",Molex_Micro-Fit_3.0_43650-0615_1x06_P3.00mm_Vertical,C505231
TERM,"JP1,JP2",PinHeader_1x02_P2.54mm_Vertical,C492401
ACT45B-510,"L1,L2,L3,L4,L5,L6,L7,L8",IND-SMD_4P-L4.5-W3.2-TL,C76584
AO3401A,Q1,SOT-23,C15127
10k,R1,R_0603_1608Metric,C25804
1k,"R2,R23,R33,R43,R53,R63,R73,R83,R93",R_0603_1608Metric,C21190
100k,"R20,R30,R40,R50,R60,R70,R80,R90",R_0603_1608Metric,C25803
47k,"R21,R31,R41,R51,R61,R71,R81,R91",R_0603_1608Metric,C25819
2.2k,"R22,R32,R42,R52,R62,R72,R82,R92",R_0603_1608Metric,C4190
60.4Ω,"R3,R4,R5,R6",R_0603_1608Metric,C4099359
TPS259531,"U1,U2,U3,U4,U5,U6,U7,U8",Texas_DSG0008A_WSON-8-1EP_2x2mm_P0.5mm_EP0.9x1.6mm,C2155674

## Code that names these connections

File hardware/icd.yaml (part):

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          4: {net: SPI_MISO, wire: vert}
          5: {net: SPI_MOSI, wire: bleu}
          6: {net: SPI_CS,   wire: gris}
          7: {net: IMU_INT,  wire: jaune_liseré,   note: "H_INTN, actif bas, GPIO à capacité de réveil"}
          8: {net: IMU_WAKE, wire: bleu, note: "PS0/WAKE — GPIO obligatoire"}

      J18:
        name: FANS
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      GPIO2: "NC — un pull-up externe empêcherait le download boot"

    assignments:
      GPIO5:  {net: CAN_TX,     note: "strapping, doit être HAUT au boot -> pull-up 10k vers 3V3"}
      GPIO4:  {net: CAN_RX,     note: "TCAN1042HV. STB DOIT ÊTRE TIRÉ À GND (pull-up interne = standby)"}
      GPIO21: {net: I2C_SDA,    note: "MCP4728 + ADS1115"}
      GPIO22: {net: I2C_SCL,    note: ""}
      GPIO34: {net: HALL_A1,    note: "entrée seule — sortie push-pull du LVC3G17, aucun pull externe requis"}
      GPIO35: {net: HALL_B1,    note: "entrée seule"}
      GPIO36: {net: HALL_C1,    note: "entrée seule (SENSOR_VP)"}
      GPIO39: {net: HALL_A2,    note: "entrée seule (SENSOR_VN)"}
      GPIO32: {net: HALL_B2,    note: ""}
      GPIO33: {net: HALL_C2,    note: ""}
      GPIO25: {net: DIR_1,      note: "DMG1012T drain ouvert — PAS de 2N7002"}
      GPIO14: {net: DIR_2,      note: ""}
      GPIO27: {net: STOP_1,     note: "commande seule, aucun rôle de sécurité"}
      GPIO23: {net: STOP_2,     note: "séparés par roue : permet de désactiver UNE roue en mode DEGRADED (§M.4)"}
      GPIO26: {net: BRAKE_RELEASE, note: "COMMUN AUX DEUX ROUES. Entrée de la porte ET 74LVC1G08. Pull-down 100k obligatoire"}
      GPIO19: {net: SAFE_N_IN,  note: "interruption. Ligne référencée 3V3, pull-down faible 1M local"}
      GPIO18: {net: WD_DONE,    note: "TPL5010 — reconnu sur transition BAS->HAUT, >= 20 ms avant le prochain WAKE"}
      GPIO13: {net: WD_WAKE,    note: "TPL5010 — impulsion de 20 ms au début de chaque intervalle"}
      GPIO15: {net: LED_STATUS, note: "LED anode->3V3 via R, cathode->GPIO. Pull-up interne = LED éteinte au boot, log de boot préservé"}

    spare:
      GPIO16: {status: conditional, blocked_by: P3, note: "INUTILISABLE sur variante D0WDR2-V3 (PSRAM). Réserve conditionnelle"}
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
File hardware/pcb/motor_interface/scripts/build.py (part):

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P_OPA = ("Amplifier_Operational:TLV9062xD", "Package_SO:SOIC-8_3.9x4.9mm_P1.27mm", "TLV9062IDR", "C398355",
         "TI TLV9062IDR")
P_CAN = ("Interface_CAN_LIN:TJA1042T-3", "Package_SO:SOIC-8_3.9x4.9mm_P1.27mm", "TCAN1042HVDR", "C127869",
         "TI TCAN1042HVDR")   # pin-compatible symbol: TXD GND VCC RXD VIO CANL CANH STB
P_CMC = ("Filter:Choke_CommonMode_FerriteCore_1423", "lcsc:IND-SMD_4P-L4.5-W3.2-TL",
         "ACT45B-510", "C76584", "TDK ACT45B-510-2P-TL003")
P_CANESD = ("Power_Protection:NUP2105L", "Package_TO_SOT_SMD:SOT-23", "NUP2105L", "C14486", "onsemi NUP2105LT1G")
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          "7": None,            # GND in the user guide, unlabeled in the schematic: left open (P2)
          "8": "SAFE_N_IN", "9": "WD_DONE", "10": "CAN_TX",
          "11": None, "12": None,                 # IO17/IO16: reserve, PSRAM variant (P3)
          "13": "CAN_RX", "14": None, "15": None,  # IO0/IO2 strapping: NC
          "16": "LED_STATUS", "17": None, "18": None, "19": None}
    c.add("J10", P_SOCK, j2, pcb=(MOD_PIN1_X, MOD_ROW_TOP), rot=270, value="DevKitC J2 (3V3…5V)", size=(60, 60))
    c.add("J11", P_SOCK, j3, pcb=(MOD_PIN1_X, MOD_ROW_BOT), rot=270, value="DevKitC J3 (GND…CLK)", size=(60, 60))
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    c.block("CAN — TCAN1042HVDR, STB à la masse, VIO 3,3 V, pas de terminaison sur cette carte", 30, 200, 260)
    c.add("U2", P_CAN, {"1": "CAN_TX", "2": "GND", "3": "+5V", "4": "CAN_RX", "5": "+3V3", "6": "CANL_T",
                        "7": "CANH_T", "8": "GND"}, pcb=(27.0, 53.0), rot=90)
    c.R("R4", "10k", "+3V3", "CAN_TX", pcb=(33.2, 48.4), rot=0)     # GPIO5 strapping: high at boot
    c.C("C6", "4.7u", "+5V", "GND", pcb=(21.0, 49.0), rot=90)
    c.C("C7", "100n", "+5V", "GND", pcb=(23.4, 48.4), rot=90)
    c.C("C8", "100n", "+3V3", "GND", pcb=(30.6, 48.4), rot=90)
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          pcb=(62.0, 57.0), rot=0)
    # TPL5010 SNAS651A table 3: 6.788 kΩ -> 2 s. 6.8 kΩ 1 % gives ~2.0 s.
    c.R("R8", "6.8k", "WD_DELAY", "GND", pcb=(58.0, 57.0), rot=90)
    c.R("R9", "100k", "WD_DONE", "GND", pcb=(65.8, 60.0), rot=0)   # no DONE edge while GPIO18 floats
    c.R("R10", "100k", "+3V3", "ESP_EN", pcb=(62.0, 60.0), rot=0)    # RSTn open drain: TI recommends 100k
    c.C("C10", "100n", "+3V3", "GND", pcb=(62.0, 54.0), rot=0)

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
